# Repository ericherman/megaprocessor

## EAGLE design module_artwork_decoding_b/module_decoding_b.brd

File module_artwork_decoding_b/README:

Decode B

This bundles together signals from the Opcode Decode module for routing
to other modules. In particular the Status Flags Calculation, ALU
Control and Rnx Control modules. As well as routing it also generates
some signals required by both those modules to begin the task of working
out what needs to be done this cycle.

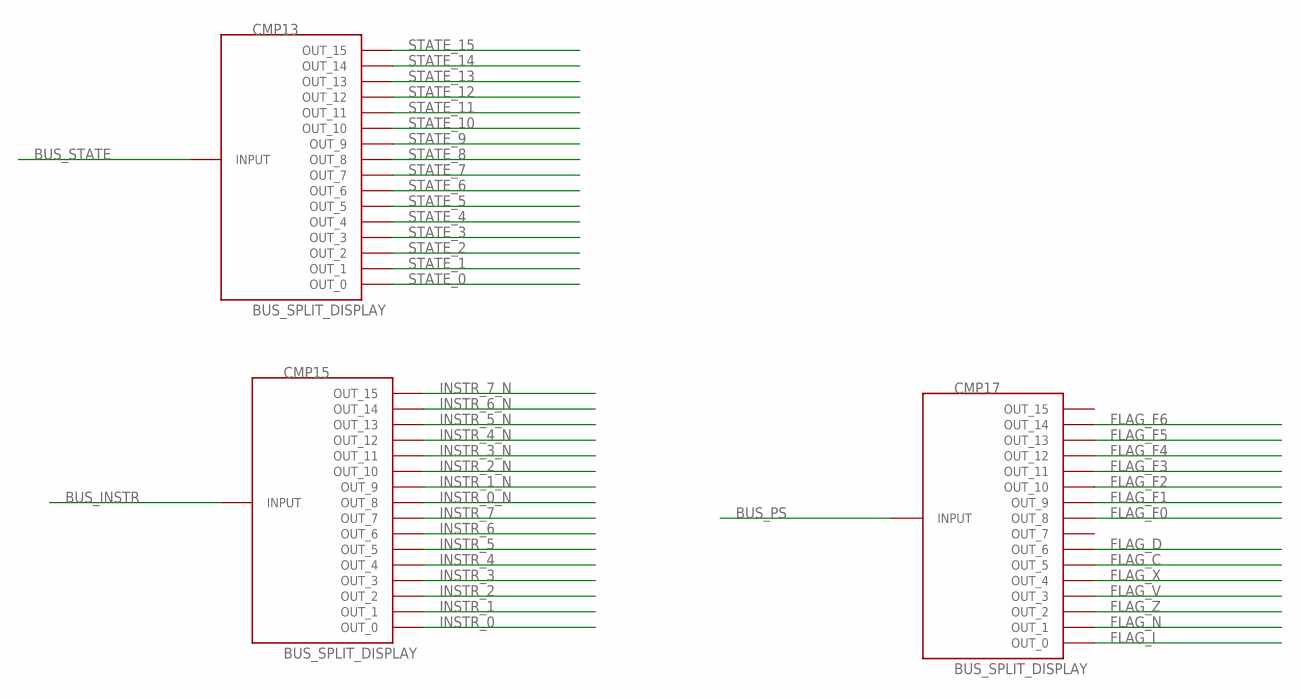
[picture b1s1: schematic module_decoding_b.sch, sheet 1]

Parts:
CMP13, CMP15, CMP17: BUS_SPLIT_DISPLAY

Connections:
BUS_INSTR: CMP15.INPUT
BUS_PS: CMP17.INPUT
BUS_STATE: CMP13.INPUT
FLAG_C: CMP17.P$6 (OUT_5)
FLAG_D: CMP17.P$7 (OUT_6)
FLAG_F0: CMP17.P$9 (OUT_8); also elsewhere on the board
FLAG_F1: CMP17.P$10 (OUT_9); also elsewhere on the board
FLAG_F2: CMP17.P$11 (OUT_10)
FLAG_F3: CMP17.P$12 (OUT_11); also elsewhere on the board
FLAG_F4: CMP17.P$13 (OUT_12)
FLAG_F5: CMP17.P$14 (OUT_13)
FLAG_F6: CMP17.P$15 (OUT_14)
FLAG_I: CMP17.P$1 (OUT_0)
FLAG_N: CMP17.P$2 (OUT_1)
FLAG_V: CMP17.P$4 (OUT_3)
FLAG_X: CMP17.P$5 (OUT_4); also elsewhere on the board
FLAG_Z: CMP17.P$3 (OUT_2)
INSTR_0: CMP15.P$1 (OUT_0)
INSTR_0_N: CMP15.P$9 (OUT_8)
INSTR_1: CMP15.P$2 (OUT_1)
INSTR_1_N: CMP15.P$10 (OUT_9)
INSTR_2: CMP15.P$3 (OUT_2)
INSTR_2_N: CMP15.P$11 (OUT_10); also elsewhere on the board
INSTR_3: CMP15.P$4 (OUT_3); also elsewhere on the board
INSTR_3_N: CMP15.P$12 (OUT_11)
INSTR_4: CMP15.P$5 (OUT_4)
INSTR_4_N: CMP15.P$13 (OUT_12)
INSTR_5: CMP15.P$6 (OUT_5)
INSTR_5_N: CMP15.P$14 (OUT_13)
INSTR_6: CMP15.P$7 (OUT_6)
INSTR_6_N: CMP15.P$15 (OUT_14)
INSTR_7: CMP15.P$8 (OUT_7)
INSTR_7_N: CMP15.P$16 (OUT_15)
STATE_0: CMP13.P$1 (OUT_0); also elsewhere on the board
STATE_1: CMP13.P$2 (OUT_1)
STATE_2: CMP13.P$3 (OUT_2); also elsewhere on the board
STATE_3: CMP13.P$4 (OUT_3); also elsewhere on the board
STATE_4: CMP13.P$5 (OUT_4)
STATE_5: CMP13.P$6 (OUT_5); also elsewhere on the board
STATE_6: CMP13.P$7 (OUT_6)
STATE_7: CMP13.P$8 (OUT_7); also elsewhere on the board
STATE_8: CMP13.P$9 (OUT_8)
STATE_9: CMP13.P$10 (OUT_9)
STATE_10: CMP13.P$11 (OUT_10)
STATE_11: CMP13.P$12 (OUT_11)
STATE_12: CMP13.P$13 (OUT_12)
STATE_13: CMP13.P$14 (OUT_13); also elsewhere on the board
STATE_14: CMP13.P$15 (OUT_14)
STATE_15: CMP13.P$16 (OUT_15)

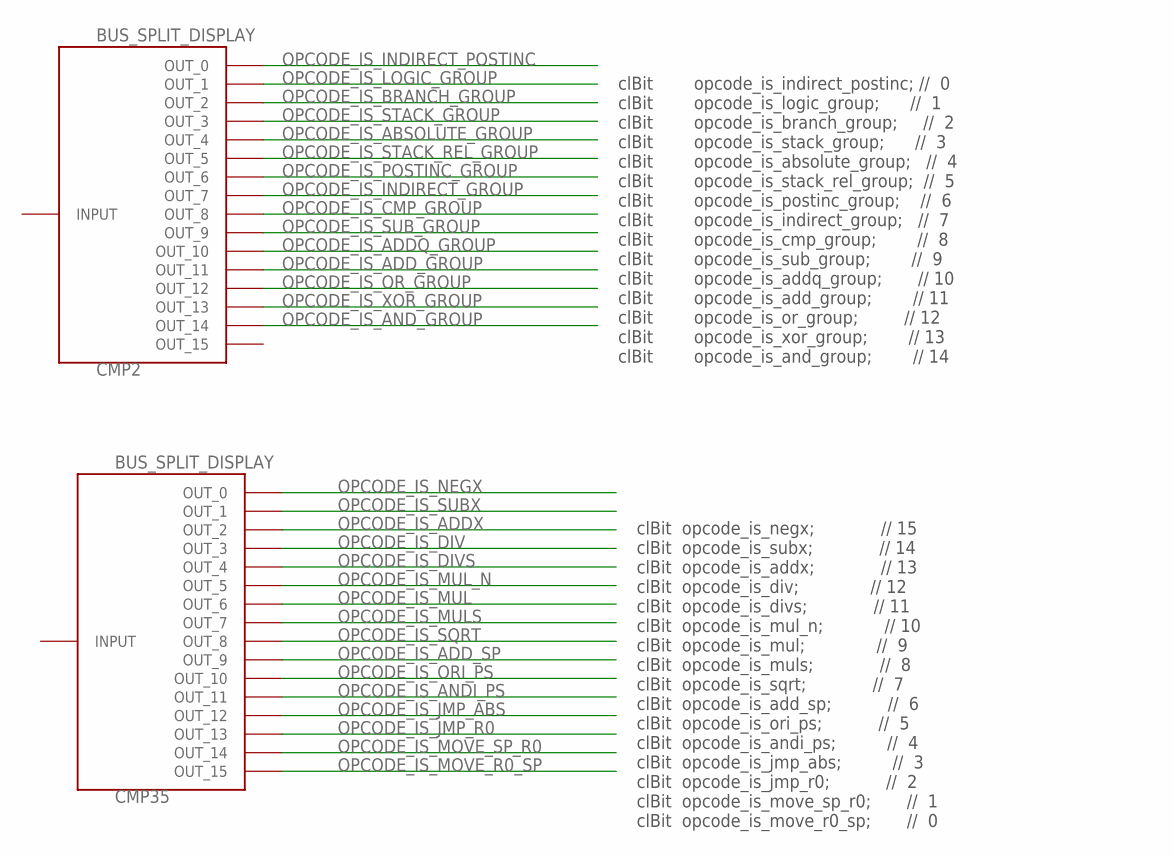
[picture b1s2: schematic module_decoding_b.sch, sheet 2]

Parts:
CMP2, CMP35: BUS_SPLIT_DISPLAY

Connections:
OPCODE_IS_ABSOLUTE_GROUP: CMP2.P$5 (OUT_4)
OPCODE_IS_ADDQ_GROUP: CMP2.P$11 (OUT_10); also elsewhere on the board
OPCODE_IS_ADDX: CMP35.P$3 (OUT_2); also elsewhere on the board
OPCODE_IS_ADD_GROUP: CMP2.P$12 (OUT_11); also elsewhere on the board
OPCODE_IS_ADD_SP: CMP35.P$10 (OUT_9); also elsewhere on the board
OPCODE_IS_ANDI_PS: CMP35.P$12 (OUT_11); also elsewhere on the board
OPCODE_IS_AND_GROUP: CMP2.P$15 (OUT_14); also elsewhere on the board
OPCODE_IS_BRANCH_GROUP: CMP2.P$3 (OUT_2); also elsewhere on the board
OPCODE_IS_CMP_GROUP: CMP2.P$9 (OUT_8); also elsewhere on the board
OPCODE_IS_DIV: CMP35.P$4 (OUT_3); also elsewhere on the board
OPCODE_IS_DIVS: CMP35.P$5 (OUT_4); also elsewhere on the board
OPCODE_IS_INDIRECT_GROUP: CMP2.P$8 (OUT_7)
OPCODE_IS_INDIRECT_POSTINC: CMP2.P$1 (OUT_0); also elsewhere on the board
OPCODE_IS_JMP_ABS: CMP35.P$13 (OUT_12)
OPCODE_IS_JMP_R0: CMP35.P$14 (OUT_13); also elsewhere on the board
OPCODE_IS_LOGIC_GROUP: CMP2.P$2 (OUT_1); also elsewhere on the board
OPCODE_IS_MOVE_R0_SP: CMP35.P$16 (OUT_15); also elsewhere on the board
OPCODE_IS_MOVE_SP_R0: CMP35.P$15 (OUT_14); also elsewhere on the board
OPCODE_IS_MUL: CMP35.P$7 (OUT_6); also elsewhere on the board
OPCODE_IS_MULS: CMP35.P$8 (OUT_7); also elsewhere on the board
OPCODE_IS_MUL_N: CMP35.P$6 (OUT_5); also elsewhere on the board
OPCODE_IS_NEGX: CMP35.P$1 (OUT_0); also elsewhere on the board
OPCODE_IS_ORI_PS: CMP35.P$11 (OUT_10); also elsewhere on the board
OPCODE_IS_OR_GROUP: CMP2.P$13 (OUT_12); also elsewhere on the board
OPCODE_IS_POSTINC_GROUP: CMP2.P$7 (OUT_6); also elsewhere on the board
OPCODE_IS_SQRT: CMP35.P$9 (OUT_8); also elsewhere on the board
OPCODE_IS_STACK_GROUP: CMP2.P$4 (OUT_3); also elsewhere on the board
OPCODE_IS_STACK_REL_GROUP: CMP2.P$6 (OUT_5); also elsewhere on the board
OPCODE_IS_SUBX: CMP35.P$2 (OUT_1); also elsewhere on the board
OPCODE_IS_SUB_GROUP: CMP2.P$10 (OUT_9); also elsewhere on the board
OPCODE_IS_XOR_GROUP: CMP2.P$14 (OUT_13); also elsewhere on the board

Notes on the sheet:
clBit opcode_is_indirect_postinc; // 0 clBit opcode_is_logic_group; // 1 clBit opcode_is_branch_group; // 2 clBit opcode_is_stack_group; // 3 clBit opcode_is_absolute_group; // 4 clBit opcode_is_stack_rel_group; // 5 clBit opcode_is_postinc_group; // 6 clBit opcode_is_indirect_group; // 7 clBit opc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
clBit opcode_is_negx; // 15 clBit opcode_is_subx; // 14 clBit opcode_is_addx; // 13 clBit opcode_is_div; // 12 clBit opcode_is_divs; // 11 clBit opcode_is_mul_n; // 10 clBit opcode_is_mul; // 9 clBit opcode_is_muls; // 8 clBit opcode_is_sqrt; // 7 clBit opcode_is_add_sp; // 6 clBit opcode_is_ori_ps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

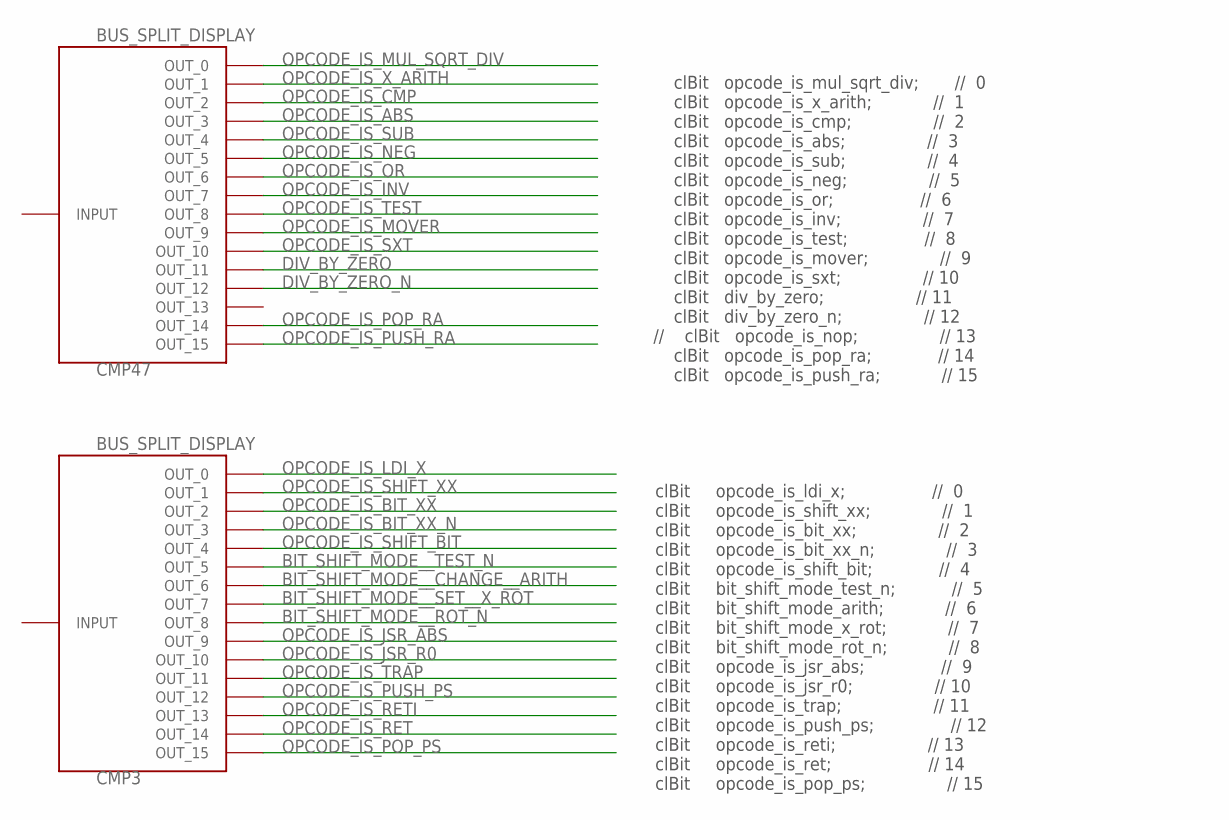
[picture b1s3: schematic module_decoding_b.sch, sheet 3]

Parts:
CMP3, CMP47: BUS_SPLIT_DISPLAY

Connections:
BIT_SHIFT_MODE__CHANGE__ARITH: CMP3.P$7 (OUT_6); also elsewhere on the board
BIT_SHIFT_MODE__ROT_N: CMP3.P$9 (OUT_8); also elsewhere on the board
BIT_SHIFT_MODE__SET__X_ROT: CMP3.P$8 (OUT_7); also elsewhere on the board
BIT_SHIFT_MODE__TEST_N: CMP3.P$6 (OUT_5); also elsewhere on the board
DIV_BY_ZERO: CMP47.P$12 (OUT_11); also elsewhere on the board
DIV_BY_ZERO_N: CMP47.P$13 (OUT_12); also elsewhere on the board
OPCODE_IS_ABS: CMP47.P$4 (OUT_3); also elsewhere on the board
OPCODE_IS_BIT_XX: CMP3.P$3 (OUT_2); also elsewhere on the board
OPCODE_IS_BIT_XX_N: CMP3.P$4 (OUT_3); also elsewhere on the board
OPCODE_IS_CMP: CMP47.P$3 (OUT_2); also elsewhere on the board
OPCODE_IS_INV: CMP47.P$8 (OUT_7); also elsewhere on the board
OPCODE_IS_JSR_ABS: CMP3.P$10 (OUT_9); also elsewhere on the board
OPCODE_IS_JSR_R0: CMP3.P$11 (OUT_10); also elsewhere on the board
OPCODE_IS_LDI_X: CMP3.P$1 (OUT_0); also elsewhere on the board
OPCODE_IS_MOVER: CMP47.P$10 (OUT_9); also elsewhere on the board
OPCODE_IS_MUL_SQRT_DIV: CMP47.P$1 (OUT_0); also elsewhere on the board
OPCODE_IS_NEG: CMP47.P$6 (OUT_5); also elsewhere on the board
OPCODE_IS_OR: CMP47.P$7 (OUT_6); also elsewhere on the board
OPCODE_IS_POP_PS: CMP3.P$16 (OUT_15); also elsewhere on the board
OPCODE_IS_POP_RA: CMP47.P$15 (OUT_14); also elsewhere on the board
OPCODE_IS_PUSH_PS: CMP3.P$13 (OUT_12); also elsewhere on the board
OPCODE_IS_PUSH_RA: CMP47.P$16 (OUT_15); also elsewhere on the board
OPCODE_IS_RET: CMP3.P$15 (OUT_14); also elsewhere on the board
OPCODE_IS_RETI: CMP3.P$14 (OUT_13); also elsewhere on the board
OPCODE_IS_SHIFT_BIT: CMP3.P$5 (OUT_4); also elsewhere on the board
OPCODE_IS_SHIFT_XX: CMP3.P$2 (OUT_1); also elsewhere on the board
OPCODE_IS_SUB: CMP47.P$5 (OUT_4); also elsewhere on the board
OPCODE_IS_SXT: CMP47.P$11 (OUT_10); also elsewhere on the board
OPCODE_IS_TEST: CMP47.P$9 (OUT_8); also elsewhere on the board
OPCODE_IS_TRAP: CMP3.P$12 (OUT_11); also elsewhere on the board
OPCODE_IS_X_ARITH: CMP47.P$2 (OUT_1); also elsewhere on the board

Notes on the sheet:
clBit opcode_is_ldi_x; // 0 clBit opcode_is_shift_xx; // 1 clBit opcode_is_bit_xx; // 2 clBit opcode_is_bit_xx_n; // 3 clBit opcode_is_shift_bit; // 4 clBit bit_shift_mode_test_n; // 5 clBit bit_shift_mode_arith; // 6 clBit bit_shift_mode_x_rot; // 7 clBit bit_shift_mode_rot_n; // 8 clBit opcode_is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
clBit opcode_is_mul_sqrt_div; // 0 clBit opcode_is_x_arith; // 1 clBit opcode_is_cmp; // 2 clBit opcode_is_abs; // 3 clBit opcode_is_sub; // 4 clBit opcode_is_neg; // 5 clBit opcode_is_or; // 6 clBit opcode_is_inv; // 7 clBit opcode_is_test; // 8 clBit opcode_is_mover; // 9 clBit opcode_is_sxt; // 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

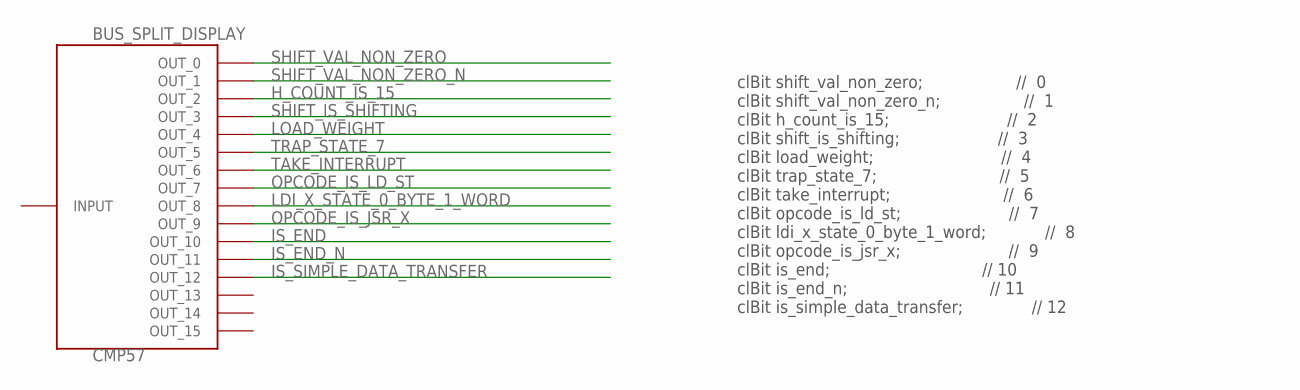
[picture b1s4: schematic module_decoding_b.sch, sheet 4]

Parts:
CMP57: BUS_SPLIT_DISPLAY

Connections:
H_COUNT_IS_15: CMP57.P$3 (OUT_2); also elsewhere on the board
IS_END: CMP57.P$11 (OUT_10)
IS_END_N: CMP57.P$12 (OUT_11); also elsewhere on the board
IS_SIMPLE_DATA_TRANSFER: CMP57.P$13 (OUT_12)
LDI_X_STATE_0_BYTE_1_WORD: CMP57.P$9 (OUT_8); also elsewhere on the board
LOAD_WEIGHT: CMP57.P$5 (OUT_4); also elsewhere on the board
OPCODE_IS_JSR_X: CMP57.P$10 (OUT_9); also elsewhere on the board
OPCODE_IS_LD_ST: CMP57.P$8 (OUT_7); also elsewhere on the board
SHIFT_IS_SHIFTING: CMP57.P$4 (OUT_3); also elsewhere on the board
SHIFT_VAL_NON_ZERO: CMP57.P$1 (OUT_0)
SHIFT_VAL_NON_ZERO_N: CMP57.P$2 (OUT_1)
TAKE_INTERRUPT: CMP57.P$7 (OUT_6); also elsewhere on the board
TRAP_STATE_7: CMP57.P$6 (OUT_5); also elsewhere on the board

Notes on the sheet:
clBit shift_val_non_zero; // 0 clBit shift_val_non_zero_n; // 1 clBit h_count_is_15; // 2 clBit shift_is_shifting; // 3 clBit load_weight; // 4 clBit trap_state_7; // 5 clBit take_interrupt; // 6 clBit opcode_is_ld_st; // 7 clBit ldi_x_state_0_byte_1_word; // 8 clBit opcode_is_jsr_x; // 9 clBit is_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

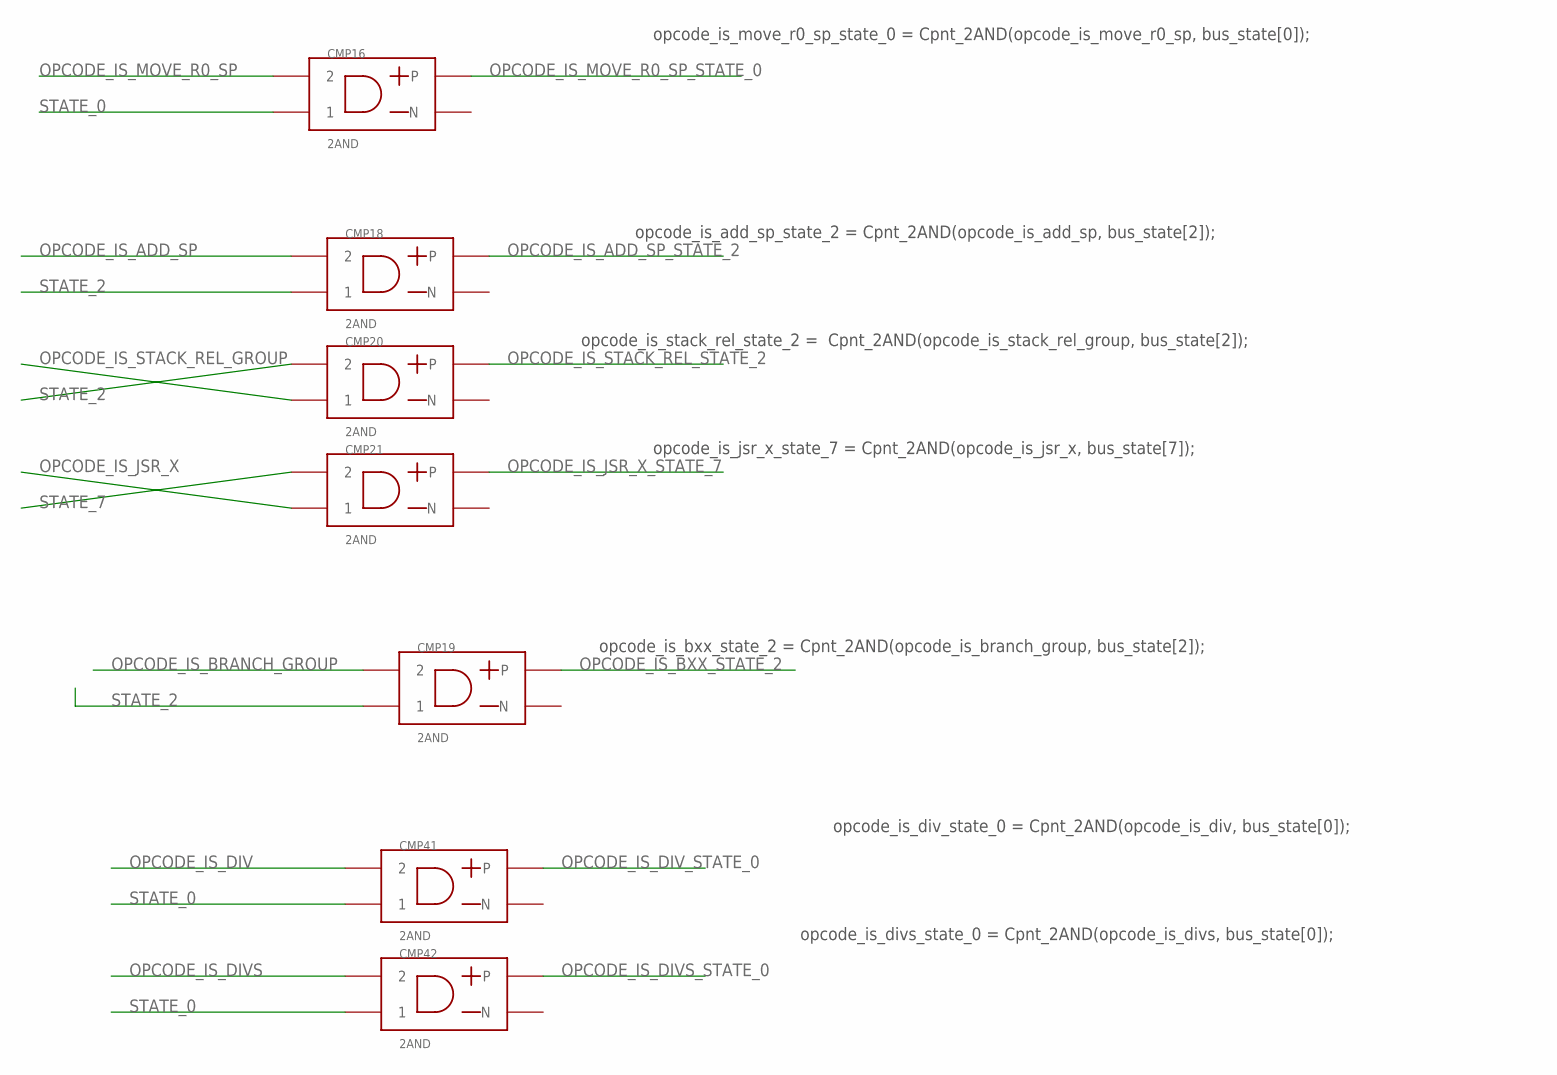
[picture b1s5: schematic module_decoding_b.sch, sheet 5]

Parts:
CMP16, CMP18, CMP19, CMP20, CMP21, CMP41, CMP42: 2AND

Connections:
OPCODE_IS_ADD_SP: CMP18.P$2 (2); also elsewhere on the board
OPCODE_IS_ADD_SP_STATE_2: CMP18.OUT_P; also elsewhere on the board
OPCODE_IS_BRANCH_GROUP: CMP19.P$2 (2); also elsewhere on the board
OPCODE_IS_BXX_STATE_2: CMP19.OUT_P; also elsewhere on the board
OPCODE_IS_DIV: CMP41.P$2 (2); also elsewhere on the board
OPCODE_IS_DIVS: CMP42.P$2 (2); also elsewhere on the board
OPCODE_IS_DIVS_STATE_0: CMP42.OUT_P; also elsewhere on the board
OPCODE_IS_DIV_STATE_0: CMP41.OUT_P; also elsewhere on the board
OPCODE_IS_JSR_X: CMP21.P$1 (1); also elsewhere on the board
OPCODE_IS_JSR_X_STATE_7: CMP21.OUT_P; also elsewhere on the board
OPCODE_IS_MOVE_R0_SP: CMP16.P$2 (2); also elsewhere on the board
OPCODE_IS_MOVE_R0_SP_STATE_0: CMP16.OUT_P; also elsewhere on the board
OPCODE_IS_STACK_REL_GROUP: CMP20.P$1 (1); also elsewhere on the board
OPCODE_IS_STACK_REL_STATE_2: CMP20.OUT_P; also elsewhere on the board
STATE_0: CMP16.P$1 (1), CMP41.P$1 (1), CMP42.P$1 (1); also elsewhere on the board
STATE_2: CMP18.P$1 (1), CMP19.P$1 (1), CMP20.P$2 (2); also elsewhere on the board
STATE_7: CMP21.P$2 (2); also elsewhere on the board

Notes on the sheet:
opcode_is_div_state_0 = Cpnt_2AND(opcode_is_div, bus_state[0]);
opcode_is_divs_state_0 = Cpnt_2AND(opcode_is_divs, bus_state[0]);
opcode_is_bxx_state_2 = Cpnt_2AND(opcode_is_branch_group, bus_state[2]);
opcode_is_move_r0_sp_state_0 = Cpnt_2AND(opcode_is_move_r0_sp, bus_state[0]);
opcode_is_add_sp_state_2 = Cpnt_2AND(opcode_is_add_sp, bus_state[2]);
opcode_is_stack_rel_state_2 = Cpnt_2AND(opcode_is_stack_rel_group, bus_state[2]);
opcode_is_jsr_x_state_7 = Cpnt_2AND(opcode_is_jsr_x, bus_state[7]);

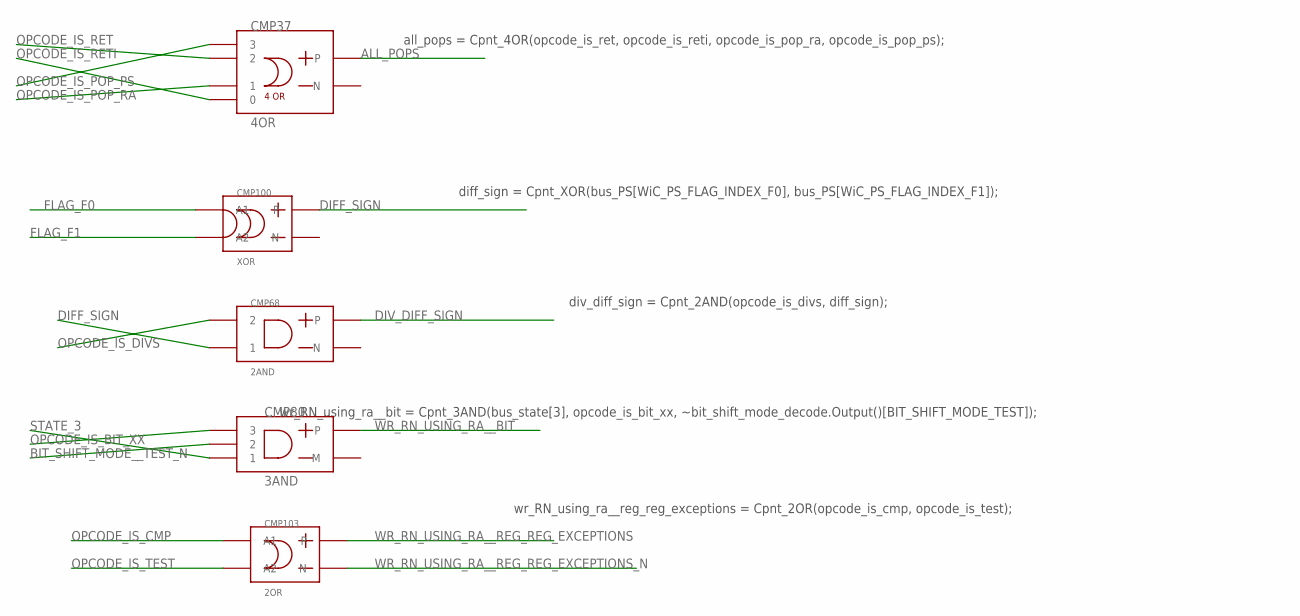
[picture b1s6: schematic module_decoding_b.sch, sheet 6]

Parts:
CMP37: 4OR
CMP68: 2AND
CMP80: 3AND
CMP100: XOR
CMP103: 2OR

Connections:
ALL_POPS: CMP37.OUT_P; also elsewhere on the board
BIT_SHIFT_MODE__TEST_N: CMP80.P$2 (2); also elsewhere on the board
DIFF_SIGN: CMP68.P$1 (1), CMP100.OUT_P
DIV_DIFF_SIGN: CMP68.OUT_P; also elsewhere on the board
FLAG_F0: CMP100.P$1 (A1); also elsewhere on the board
FLAG_F1: CMP100.P$2 (A2); also elsewhere on the board
OPCODE_IS_BIT_XX: CMP80.P$3 (3); also elsewhere on the board
OPCODE_IS_CMP: CMP103.P$2 (A1); also elsewhere on the board
OPCODE_IS_DIVS: CMP68.P$2 (2); also elsewhere on the board
OPCODE_IS_POP_PS: CMP37.4 (3); also elsewhere on the board
OPCODE_IS_POP_RA: CMP37.2 (1); also elsewhere on the board
OPCODE_IS_RET: CMP37.3 (2); also elsewhere on the board
OPCODE_IS_RETI: CMP37.1 (0); also elsewhere on the board
OPCODE_IS_TEST: CMP103.P$1 (A2); also elsewhere on the board
STATE_3: CMP80.P$1 (1); also elsewhere on the board
WR_RN_USING_RA__BIT: CMP80.OUT_P; also elsewhere on the board
WR_RN_USING_RA__REG_REG_EXCEPTIONS: CMP103.OUT_P
WR_RN_USING_RA__REG_REG_EXCEPTIONS_N: CMP103.OUT_M (N); also elsewhere on the board

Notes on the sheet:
all_pops = Cpnt_4OR(opcode_is_ret, opcode_is_reti, opcode_is_pop_ra, opcode_is_pop_ps);
div_diff_sign = Cpnt_2AND(opcode_is_divs, diff_sign);
wr_RN_using_ra__bit = Cpnt_3AND(bus_state[3], opcode_is_bit_xx, ~bit_shift_mode_decode.Output()[BIT_SHIFT_MODE_TEST]);
wr_RN_using_ra__reg_reg_exceptions = Cpnt_2OR(opcode_is_cmp, opcode_is_test);
diff_sign = Cpnt_XOR(bus_PS[WiC_PS_FLAG_INDEX_F0], bus_PS[WiC_PS_FLAG_INDEX_F1]);

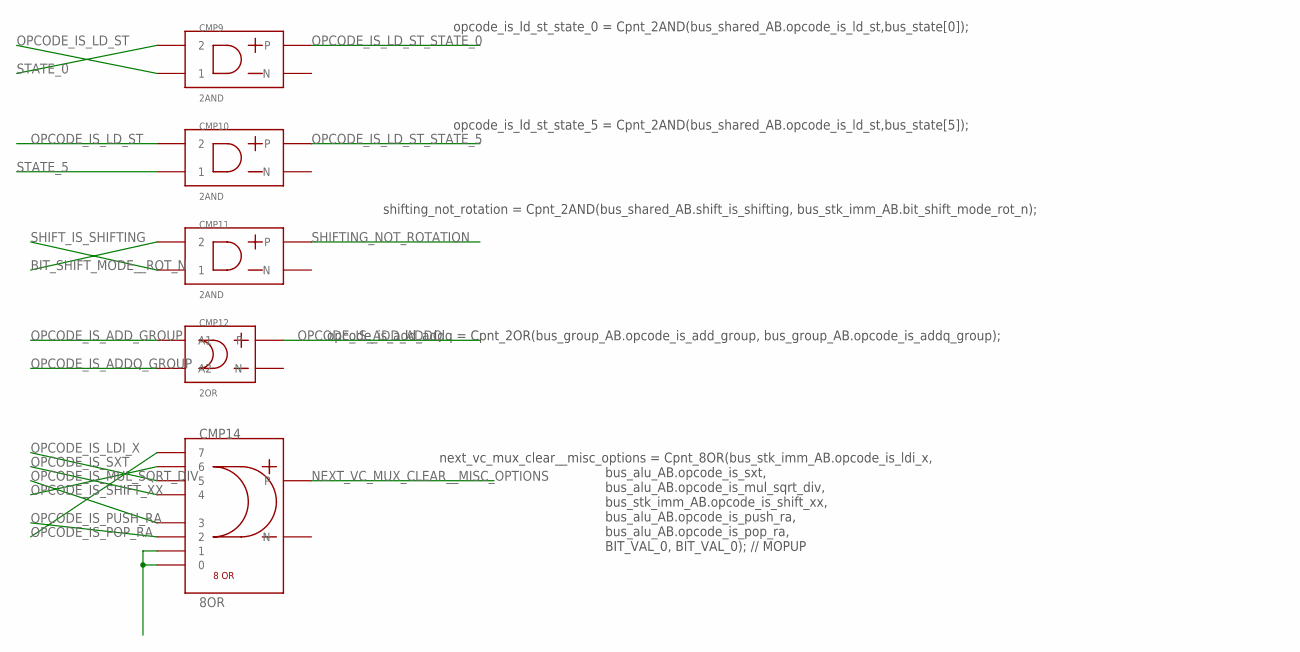
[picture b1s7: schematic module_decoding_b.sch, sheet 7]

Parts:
CMP9, CMP10, CMP11: 2AND
CMP12: 2OR
CMP14: 8OR

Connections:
BIT_SHIFT_MODE__ROT_N: CMP11.P$2 (2); also elsewhere on the board
unnamed: CMP14.1 (0), CMP14.2 (1)
NEXT_VC_MUX_CLEAR__MISC_OPTIONS: CMP14.OUT_P; also elsewhere on the board
OPCODE_IS_ADDQ_GROUP: CMP12.P$1 (A2); also elsewhere on the board
OPCODE_IS_ADD_ADDQ: CMP12.OUT_P; also elsewhere on the board
OPCODE_IS_ADD_GROUP: CMP12.P$2 (A1); also elsewhere on the board
OPCODE_IS_LDI_X: CMP14.6 (5); also elsewhere on the board
OPCODE_IS_LD_ST: CMP9.P$1 (1), CMP10.P$2 (2); also elsewhere on the board
OPCODE_IS_LD_ST_STATE_0: CMP9.OUT_P; also elsewhere on the board
OPCODE_IS_LD_ST_STATE_5: CMP10.OUT_P; also elsewhere on the board
OPCODE_IS_MUL_SQRT_DIV: CMP14.4 (3); also elsewhere on the board
OPCODE_IS_POP_RA: CMP14.8 (7); also elsewhere on the board
OPCODE_IS_PUSH_RA: CMP14.3 (2); also elsewhere on the board
OPCODE_IS_SHIFT_XX: CMP14.7 (6); also elsewhere on the board
OPCODE_IS_SXT: CMP14.5 (4); also elsewhere on the board
SHIFTING_NOT_ROTATION: CMP11.OUT_P; also elsewhere on the board
SHIFT_IS_SHIFTING: CMP11.P$1 (1); also elsewhere on the board
STATE_0: CMP9.P$2 (2); also elsewhere on the board
STATE_5: CMP10.P$1 (1); also elsewhere on the board

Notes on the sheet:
opcode_is_ld_st_state_0 = Cpnt_2AND(bus_shared_AB.opcode_is_ld_st,bus_state[0]);
opcode_is_ld_st_state_5 = Cpnt_2AND(bus_shared_AB.opcode_is_ld_st,bus_state[5]);
shifting_not_rotation = Cpnt_2AND(bus_shared_AB.shift_is_shifting, bus_stk_imm_AB.bit_shift_mode_rot_n);
opcode_is_add_addq = Cpnt_2OR(bus_group_AB.opcode_is_add_group, bus_group_AB.opcode_is_addq_group);
next_vc_mux_clear__misc_options = Cpnt_8OR(bus_stk_imm_AB.opcode_is_ldi_x, bus_alu_AB.opcode_is_sxt, bus_alu_AB.opcode_is_mul_sqrt_div, bus_stk_imm_AB.opcode_is_shift_xx, bus_alu_AB.opcode_is_push_ra, bus_alu_AB.opcode_is_pop_ra, BIT_VAL_0, BIT_VAL_0); // MOPUP

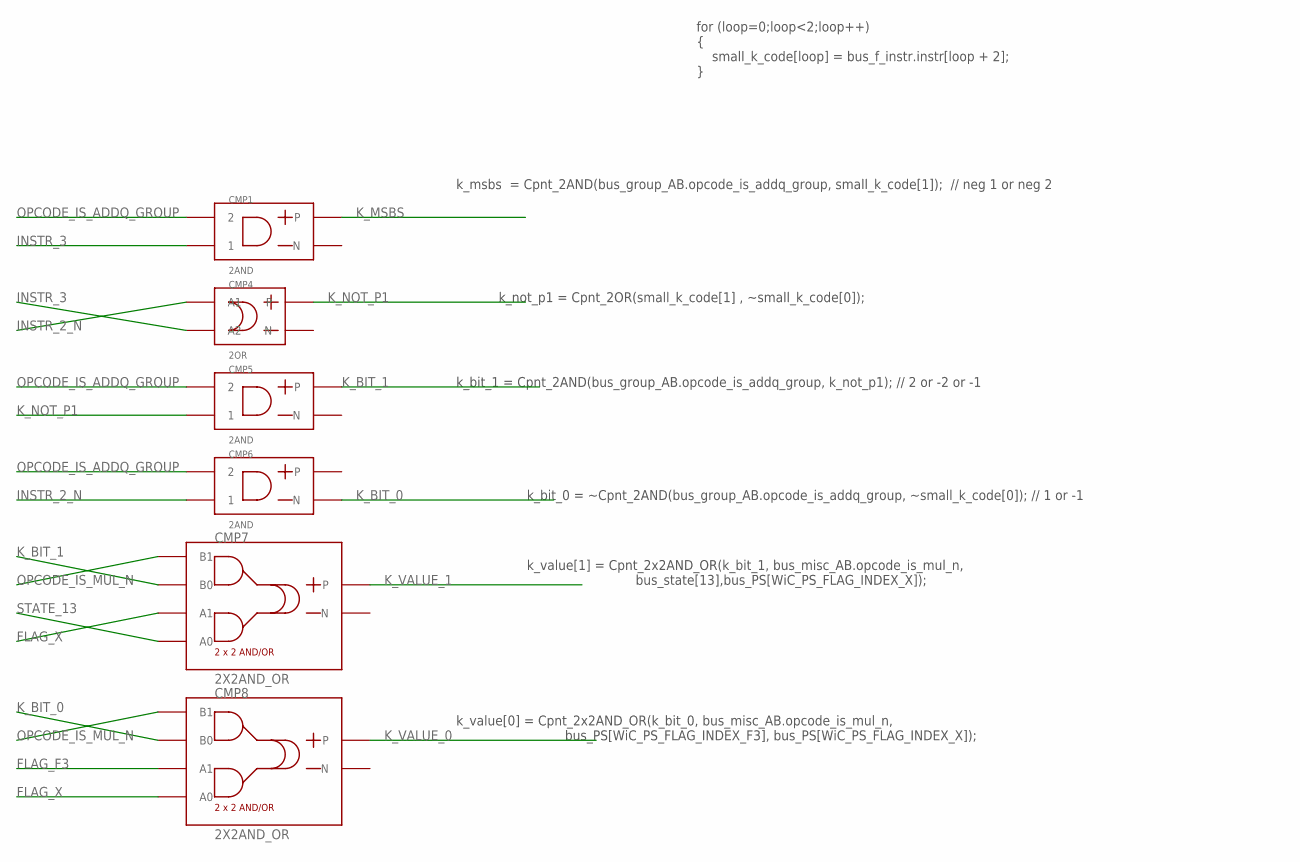
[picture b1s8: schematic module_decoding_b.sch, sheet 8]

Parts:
CMP1, CMP5, CMP6: 2AND
CMP4: 2OR
CMP7, CMP8: 2X2AND_OR

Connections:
FLAG_F3: CMP8.P$2 (A1); also elsewhere on the board
FLAG_X: CMP7.P$2 (A1), CMP8.P$1 (A0); also elsewhere on the board
INSTR_2_N: CMP4.P$2 (A1), CMP6.P$1 (1); also elsewhere on the board
INSTR_3: CMP1.P$1 (1), CMP4.P$1 (A2); also elsewhere on the board
K_BIT_0: CMP6.OUT_M (N), CMP8.P$3 (B0)
K_BIT_1: CMP5.OUT_P, CMP7.P$3 (B0)
K_MSBS: CMP1.OUT_P; also elsewhere on the board
K_NOT_P1: CMP4.OUT_P, CMP5.P$1 (1)
K_VALUE_0: CMP8.OUT_P; also elsewhere on the board
K_VALUE_1: CMP7.OUT_P; also elsewhere on the board
OPCODE_IS_ADDQ_GROUP: CMP1.P$2 (2), CMP5.P$2 (2), CMP6.P$2 (2); also elsewhere on the board
OPCODE_IS_MUL_N: CMP7.P$4 (B1), CMP8.P$4 (B1); also elsewhere on the board
STATE_13: CMP7.P$1 (A0); also elsewhere on the board

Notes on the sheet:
for (loop=0;loop<2;loop++) { small_k_code[loop] = bus_f_instr.instr[loop + 2]; }
k_msbs = Cpnt_2AND(bus_group_AB.opcode_is_addq_group, small_k_code[1]); // neg 1 or neg 2
k_not_p1 = Cpnt_2OR(small_k_code[1] , ~small_k_code[0]);
k_bit_1 = Cpnt_2AND(bus_group_AB.opcode_is_addq_group, k_not_p1); // 2 or -2 or -1
k_bit_0 = ~Cpnt_2AND(bus_group_AB.opcode_is_addq_group, ~small_k_code[0]); // 1 or -1
k_value[1] = Cpnt_2x2AND_OR(k_bit_1, bus_misc_AB.opcode_is_mul_n, bus_state[13],bus_PS[WiC_PS_FLAG_INDEX_X]);
k_value[0] = Cpnt_2x2AND_OR(k_bit_0, bus_misc_AB.opcode_is_mul_n, bus_PS[WiC_PS_FLAG_INDEX_F3], bus_PS[WiC_PS_FLAG_INDEX_X]);

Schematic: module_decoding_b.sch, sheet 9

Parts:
CMP56, CMP79: BUS_CONSTRUCT_DISPLAY; BUS_SPLIT_DISPLAY

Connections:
BIT_SHIFT_MODE__CHANGE__ARITH: CMP79.P$6 (IN_5); also elsewhere on the board
BIT_SHIFT_MODE__SET__X_ROT: CMP79.P$8 (IN_7); also elsewhere on the board
BUS_DECODE_FLAGS_1: CMP56.INPUT (OUT)
BUS_DECODE_FLAGS_2: CMP79.INPUT (OUT)
DIV_BY_ZERO: CMP79.P$10 (IN_9); also elsewhere on the board
H_COUNT_IS_15: CMP79.P$9 (IN_8); also elsewhere on the board
LDI_X_STATE_0_BYTE_1_WORD: CMP79.P$2 (IN_1); also elsewhere on the board
LOAD_WEIGHT: CMP79.P$4 (IN_3); also elsewhere on the board
unnamed: CMP79.P$13 (IN_12), CMP79.P$14 (IN_13), CMP79.P$15 (IN_14), CMP79.P$16 (IN_15)
NEXT_VC_MUX_CLEAR__MISC_OPTIONS: CMP56.P$6 (IN_5); also elsewhere on the board
OPCODE_IS_ABS: CMP56.P$13 (IN_12); also elsewhere on the board
OPCODE_IS_ADD_ADDQ: CMP56.P$9 (IN_8); also elsewhere on the board
OPCODE_IS_ANDI_PS: CMP56.P$4 (IN_3); also elsewhere on the board
OPCODE_IS_BIT_XX: CMP79.P$5 (IN_4); also elsewhere on the board
OPCODE_IS_BRANCH_GROUP: CMP56.P$1 (IN_0); also elsewhere on the board
OPCODE_IS_CMP: CMP56.P$8 (IN_7); also elsewhere on the board
OPCODE_IS_LD_ST_STATE_0: CMP56.P$16 (IN_15); also elsewhere on the board
OPCODE_IS_LD_ST_STATE_5: CMP79.P$1 (IN_0); also elsewhere on the board
OPCODE_IS_MUL_SQRT_DIV: CMP56.P$5 (IN_4); also elsewhere on the board
OPCODE_IS_NEG: CMP56.P$7 (IN_6); also elsewhere on the board
OPCODE_IS_ORI_PS: CMP56.P$3 (IN_2); also elsewhere on the board
OPCODE_IS_POP_PS: CMP56.P$2 (IN_1); also elsewhere on the board
OPCODE_IS_SHIFT_XX: CMP56.P$15 (IN_14); also elsewhere on the board
OPCODE_IS_SUB: CMP56.P$11 (IN_10); also elsewhere on the board
OPCODE_IS_SUB_GROUP: CMP56.P$10 (IN_9); also elsewhere on the board
OPCODE_IS_TRAP: CMP56.P$14 (IN_13); also elsewhere on the board
OPCODE_IS_X_ARITH: CMP56.P$12 (IN_11); also elsewhere on the board
SHIFTING_NOT_ROTATION: CMP79.P$7 (IN_6); also elsewhere on the board
SHIFT_IS_SHIFTING: CMP79.P$3 (IN_2); also elsewhere on the board
TAKE_INTERRUPT: CMP79.P$12 (IN_11); also elsewhere on the board
TRAP_STATE_7: CMP79.P$11 (IN_10); also elsewhere on the board

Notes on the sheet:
clBit opcode_is_branch_group; // 0 clBit opcode_is_pop_ps; // 1 clBit opcode_is_ori_ps; // 2 clBit opcode_is_andi_ps; // 3 clBit opcode_is_mul_sqrt_div; // 4 clBit next_vc_mux_clear__misc_options; // 5 clBit opcode_is_neg; // 6 clBit opcode_is_cmp; // 7 clBit opcode_is_add_addq; // 8 clBit opcode_i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
clBit opcode_is_ld_st_state_5; // 0 clBit ldi_x_state_0_byte_1_word; // 1 clBit shift_is_shifting; // 2 clBit load_weight; // 3 clBit opcode_is_bit_xx; // 4 clBit bit_shift_mode_arith; // 5 clBit shifting_not_rotation; // 6 clBit bit_shift_mode_x_rot; // 7 clBit h_count_is_15; // 8 clBit div_by_zer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

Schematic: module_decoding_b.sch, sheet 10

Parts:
CMP87, CMP91, CMP93: BUS_CONSTRUCT_DISPLAY; BUS_SPLIT_DISPLAY

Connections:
BUS_DECODE_ALU_1: CMP91.INPUT (OUT)
BUS_DECODE_ALU_2: CMP87.INPUT (OUT)
BUS_DECODE_ALU_3: CMP93.INPUT (OUT)
K_MSBS: CMP93.P$9 (IN_8); also elsewhere on the board
K_VALUE_0: CMP93.P$7 (IN_6); also elsewhere on the board
K_VALUE_1: CMP93.P$8 (IN_7); also elsewhere on the board
unnamed: CMP93.P$14 (IN_13), CMP93.P$15 (IN_14), CMP93.P$16 (IN_15)
OPCODE_IS_ABS: CMP87.P$14 (IN_13); also elsewhere on the board
OPCODE_IS_ADDQ_GROUP: CMP93.P$6 (IN_5); also elsewhere on the board
OPCODE_IS_ADDX: CMP87.P$12 (IN_11); also elsewhere on the board
OPCODE_IS_ADD_GROUP: CMP87.P$9 (IN_8); also elsewhere on the board
OPCODE_IS_ADD_SP_STATE_2: CMP91.P$15 (IN_14); also elsewhere on the board
OPCODE_IS_AND_GROUP: CMP87.P$8 (IN_7); also elsewhere on the board
OPCODE_IS_BIT_XX: CMP87.P$5 (IN_4); also elsewhere on the board
OPCODE_IS_BIT_XX_N: CMP93.P$2 (IN_1); also elsewhere on the board
OPCODE_IS_BXX_STATE_2: CMP87.P$1 (IN_0); also elsewhere on the board
OPCODE_IS_CMP: CMP93.P$1 (IN_0); also elsewhere on the board
OPCODE_IS_CMP_GROUP: CMP93.P$10 (IN_9); also elsewhere on the board
OPCODE_IS_DIV: CMP87.P$15 (IN_14); also elsewhere on the board
OPCODE_IS_DIVS_STATE_0: CMP91.P$2 (IN_1); also elsewhere on the board
OPCODE_IS_DIV_STATE_0: CMP91.P$7 (IN_6); also elsewhere on the board
OPCODE_IS_INDIRECT_POSTINC: CMP91.P$9 (IN_8); also elsewhere on the board
OPCODE_IS_INV: CMP93.P$3 (IN_2); also elsewhere on the board
OPCODE_IS_JMP_R0: CMP91.P$11 (IN_10); also elsewhere on the board
OPCODE_IS_JSR_ABS: CMP91.P$14 (IN_13); also elsewhere on the board
OPCODE_IS_JSR_R0: CMP91.P$5 (IN_4); also elsewhere on the board
OPCODE_IS_JSR_X_STATE_7: CMP91.P$8 (IN_7); also elsewhere on the board
OPCODE_IS_LOGIC_GROUP: CMP87.P$3 (IN_2); also elsewhere on the board
OPCODE_IS_MOVER: CMP93.P$11 (IN_10); also elsewhere on the board
OPCODE_IS_MOVE_R0_SP_STATE_0: CMP91.P$12 (IN_11); also elsewhere on the board
OPCODE_IS_MOVE_SP_R0: CMP91.P$10 (IN_9); also elsewhere on the board
OPCODE_IS_MULS: CMP87.P$13 (IN_12); also elsewhere on the board
OPCODE_IS_MUL_N: CMP91.P$13 (IN_12); also elsewhere on the board
OPCODE_IS_NEG: CMP87.P$4 (IN_3); also elsewhere on the board
OPCODE_IS_NEGX: CMP87.P$10 (IN_9); also elsewhere on the board
OPCODE_IS_OR: CMP87.P$7 (IN_6); also elsewhere on the board
OPCODE_IS_OR_GROUP: CMP93.P$12 (IN_11); also elsewhere on the board
OPCODE_IS_PUSH_PS: CMP91.P$3 (IN_2); also elsewhere on the board
OPCODE_IS_PUSH_RA: CMP91.P$4 (IN_3); also elsewhere on the board
OPCODE_IS_SHIFT_XX: CMP87.P$2 (IN_1); also elsewhere on the board
OPCODE_IS_SQRT: CMP87.P$16 (IN_15); also elsewhere on the board
OPCODE_IS_STACK_GROUP: CMP93.P$5 (IN_4); also elsewhere on the board
OPCODE_IS_STACK_REL_STATE_2: CMP91.P$16 (IN_15); also elsewhere on the board
OPCODE_IS_SUB: CMP87.P$6 (IN_5); also elsewhere on the board
OPCODE_IS_SUBX: CMP87.P$11 (IN_10); also elsewhere on the board
OPCODE_IS_SUB_GROUP: CMP93.P$4 (IN_3); also elsewhere on the board
OPCODE_IS_TRAP: CMP91.P$6 (IN_5); also elsewhere on the board
OPCODE_IS_XOR_GROUP: CMP93.P$13 (IN_12); also elsewhere on the board
SHIFT_IS_SHIFTING: CMP91.P$1 (IN_0); also elsewhere on the board

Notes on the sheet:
clBit opcode_is_bxx_state_2; // 0 clBit opcode_is_shift_xx; // 1 clBit opcode_is_logic_group; // 2 clBit opcode_is_neg; // 3 clBit opcode_is_bit_xx; // 4 clBit opcode_is_sub; // 5 clBit opcode_is_or; // 6 clBit opcode_is_and_group; // 7 clBit opcode_is_add_group; // 8 clBit opcode_is_negx; // 9 clB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
clBit opcode_is_cmp; // 0 clBit opcode_is_bit_xx_n; // 1 clBit opcode_is_inv; // 2 clBit opcode_is_sub_group; // 3 clBit opcode_is_stack_group; // 4 clBit opcode_is_addq_group; // 5 clBit k_0; // 6 clBit k_1; // 7 clBit k_m; // 8 clBit opcode_is_cmp_group; // 9 clBit opcode_is_mover; // 10 clBit op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
clBit shift_is_shifting; // 0 clBit opcode_is_divs_state_0; // 1 clBit opcode_is_push_ps; // 2 clBit opcode_is_push_ra; // 3 clBit opcode_is_jsr_r0; // 4 clBit opcode_is_trap; // 5 clBit opcode_is_div_state_0; // 6 clBit opcode_is_jsr_x_state_7; // 7 clBit opcode_is_indirect_postinc; // 8 clBit opc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

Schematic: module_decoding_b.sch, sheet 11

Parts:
CMP95, CMP99: BUS_CONSTRUCT_DISPLAY; BUS_SPLIT_DISPLAY

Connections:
ALL_POPS: CMP95.P$1 (IN_0); also elsewhere on the board
BUS_DECODE_RNX_1: CMP95.INPUT (OUT)
BUS_DECODE_RNX_2: CMP99.INPUT (OUT)
DIV_BY_ZERO_N: CMP99.P$9 (IN_8); also elsewhere on the board
DIV_DIFF_SIGN: CMP99.P$13 (IN_12); also elsewhere on the board
IS_END_N: CMP95.P$14 (IN_13); also elsewhere on the board
LOAD_WEIGHT: CMP99.P$14 (IN_13); also elsewhere on the board
OPCODE_IS_ADDX: CMP95.P$3 (IN_2); also elsewhere on the board
OPCODE_IS_ADD_SP_STATE_2: CMP95.P$8 (IN_7); also elsewhere on the board
OPCODE_IS_DIV: CMP99.P$6 (IN_5); also elsewhere on the board
OPCODE_IS_DIVS_STATE_0: CMP95.P$16 (IN_15); also elsewhere on the board
OPCODE_IS_DIV_STATE_0: CMP99.P$10 (IN_9); also elsewhere on the board
OPCODE_IS_INDIRECT_POSTINC: CMP99.P$1 (IN_0); also elsewhere on the board
OPCODE_IS_JSR_ABS: CMP95.P$15 (IN_14); also elsewhere on the board
OPCODE_IS_JSR_R0: CMP99.P$3 (IN_2); also elsewhere on the board
OPCODE_IS_LDI_X: CMP99.P$11 (IN_10); also elsewhere on the board
OPCODE_IS_LD_ST: CMP99.P$4 (IN_3); also elsewhere on the board
OPCODE_IS_MOVE_R0_SP_STATE_0: CMP95.P$9 (IN_8); also elsewhere on the board
OPCODE_IS_MUL: CMP95.P$10 (IN_9); also elsewhere on the board
OPCODE_IS_MULS: CMP95.P$5 (IN_4); also elsewhere on the board
OPCODE_IS_NEGX: CMP95.P$6 (IN_5); also elsewhere on the board
OPCODE_IS_POP_PS: CMP99.P$5 (IN_4); also elsewhere on the board
OPCODE_IS_POSTINC_GROUP: CMP99.P$15 (IN_14); also elsewhere on the board
OPCODE_IS_SHIFT_BIT: CMP95.P$4 (IN_3); also elsewhere on the board
OPCODE_IS_SQRT: CMP95.P$12 (IN_11); also elsewhere on the board
OPCODE_IS_STACK_GROUP: CMP95.P$13 (IN_12); also elsewhere on the board
OPCODE_IS_STACK_REL_STATE_2: CMP95.P$11 (IN_10); also elsewhere on the board
OPCODE_IS_SUBX: CMP95.P$2 (IN_1); also elsewhere on the board
OPCODE_IS_SXT: CMP95.P$7 (IN_6); also elsewhere on the board
OPCODE_IS_TRAP: CMP99.P$2 (IN_1); also elsewhere on the board
OPCODE_IS_X_ARITH: CMP99.P$16 (IN_15); also elsewhere on the board
SHIFT_IS_SHIFTING: CMP99.P$8 (IN_7); also elsewhere on the board
WR_RN_USING_RA__BIT: CMP99.P$7 (IN_6); also elsewhere on the board
WR_RN_USING_RA__REG_REG_EXCEPTIONS_N: CMP99.P$12 (IN_11); also elsewhere on the board

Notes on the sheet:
clBit all_pops; // 0 clBit opcode_is_subx; // 1 clBit opcode_is_addx; // 2 clBit opcode_is_shift_bit; // 3 clBit opcode_is_muls; // 4 clBit opcode_is_negx; // 5 clBit opcode_is_sxt; // 6 clBit opcode_is_add_sp_state_2; // 7 clBit opcode_is_move_r0_sp_state_0; // 8 clBit opcode_is_mul; // 9 clBit op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
clBit opcode_is_indirect_postinc; // 0 clBit opcode_is_trap; // 1 clBit opcode_is_jsr_r0; // 2 clBit opcode_is_ld_st; // 3 clBit opcode_is_pop_ps; // 4 clBit opcode_is_div; // 5 clBit wr_RN_using_ra__bit; // 6 clBit shift_is_shifting; // 7 clBit div_by_zero_n; // 8 clBit opcode_is_div_state_0; // 9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

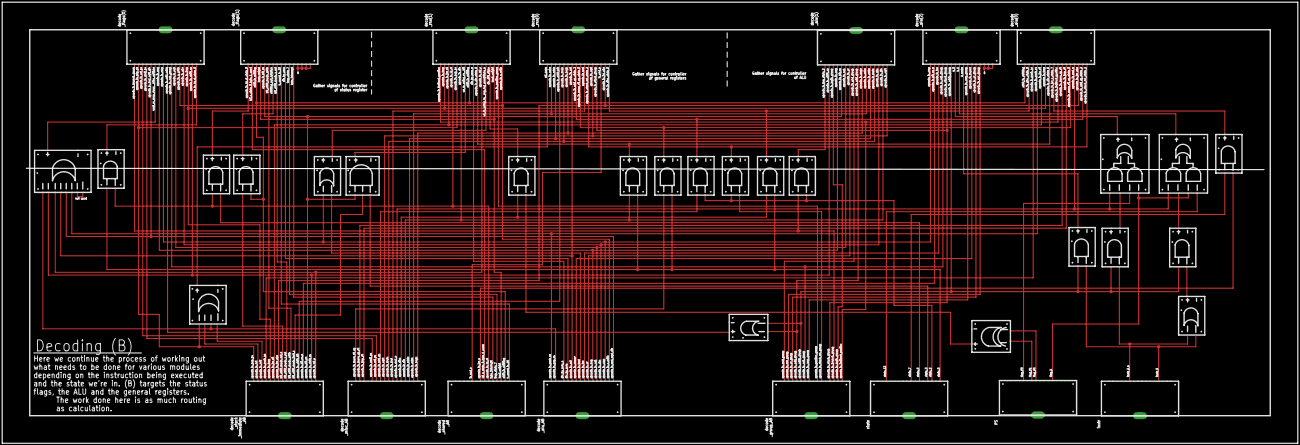
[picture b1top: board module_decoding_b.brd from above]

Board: 2 copper layers, 1193.8 x 406.4 mm, 38 parts (0 on the bottom side), 106 nets.
